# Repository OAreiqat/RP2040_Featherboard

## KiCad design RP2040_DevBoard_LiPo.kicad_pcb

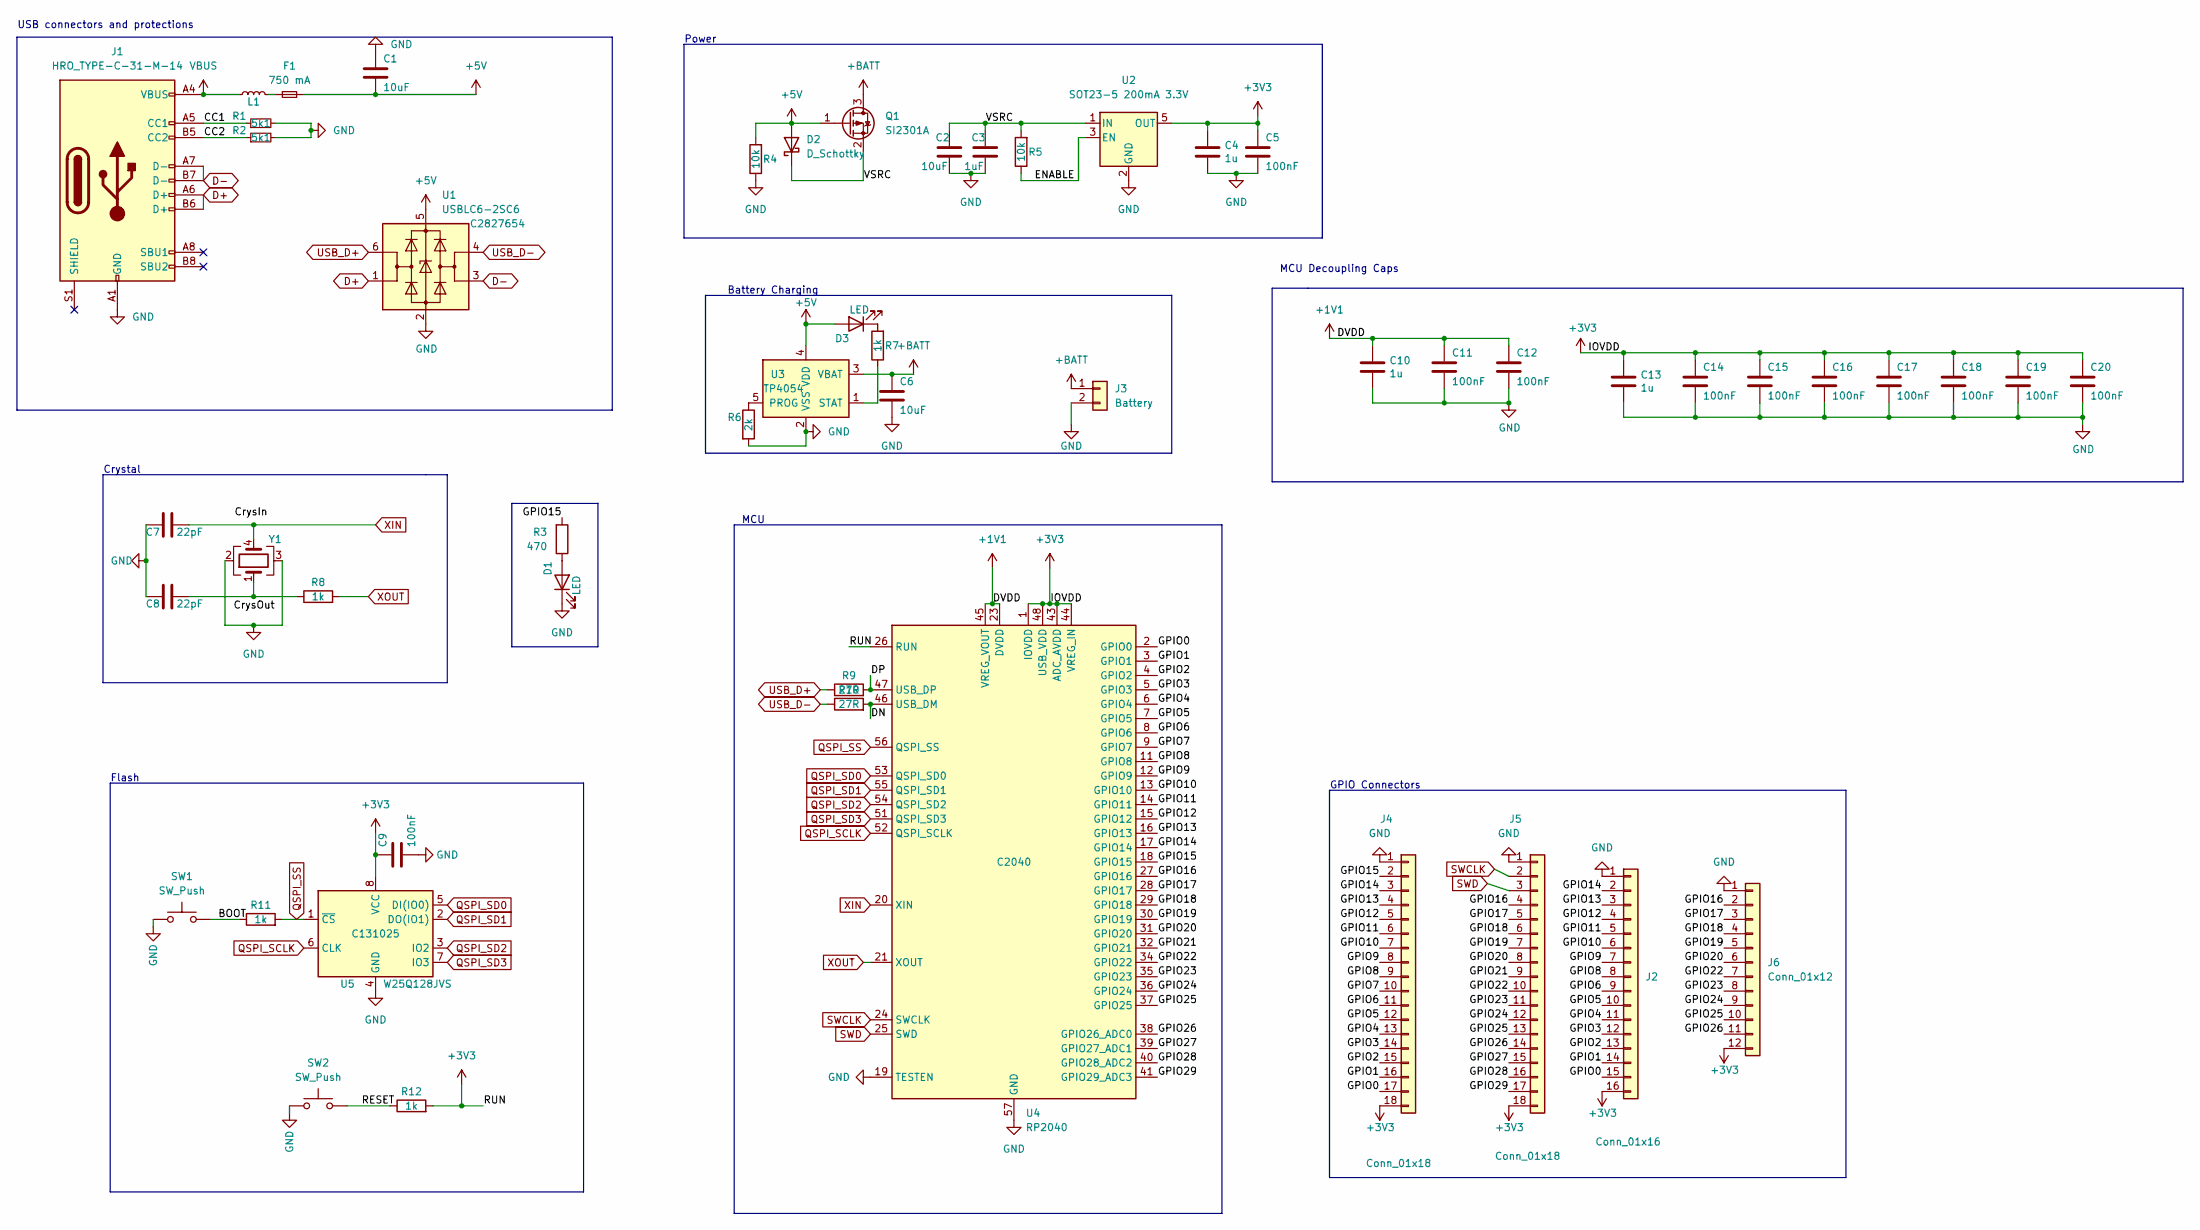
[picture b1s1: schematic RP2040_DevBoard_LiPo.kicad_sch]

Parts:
C1, C2, C6: 10uF; C_0402_1005Metric; LCSC C15525
C3: 1uF; C_0402_1005Metric; LCSC C14445
C4, C10, C13: 1u; C_0402_1005Metric; LCSC C14445
C5, C9, C11, C12, C14, C15, C16, C17, C18, C19, C20: 100nF; C_0402_1005Metric; LCSC C1525
C7, C8: 22pF; C_0402_1005Metric; LCSC C70464
D1, D3: LED; LED_1206_3216Metric; LCSC C434443
D2: D_Schottky; D_SOD-323; LCSC C22624
F1: 750 mA; Fuse_0603_1608Metric; LCSC C182438
J1: HRO_TYPE-C-31-M-14; USB_C_Receptacle_HRO_TYPE-C-31-M-12; LCSC C165948
J2: Conn_01x16; PinSocket_1x16_P2.54mm_Vertical
J3: Battery; JST_EH_S2B-EH_1x02_P2.50mm_Horizontal; LCSC C514173
J4, J5: Conn_01x18; PinSocket_1x18_P2.54mm_Vertical
J6: Conn_01x12; PinSocket_1x12_P2.54mm_Vertical
L1: BLM15PX121SN1D; L_0402_1005Metric; LCSC C88970
Q1: SI2301A; SOT-23; LCSC C347476
R1, R2: 5k1; R_0402_1005Metric; LCSC C25905
R3: 470; R_0402_1005Metric; LCSC C25117
R4, R5: 10k; R_0402_1005Metric; LCSC C60490
R6: 2k; R_0402_1005Metric; LCSC C60488
R7, R8, R11, R12: 1k; R_0402_1005Metric; LCSC C106235
R9, R10: 27R; R_0402_1005Metric; LCSC C3017455
SW1, SW2: SW_Push; SW_Push_SPST_NO_Alps_SKRK; LCSC C720477
U1: USBLC6-2SC6; SOT-23-6; LCSC C2827654
U2: SOT23-5 200mA 3.3V; SOT-23-5; LCSC C11337
U3: TP4054; SOT-23-5; LCSC C668215
U4: RP2040; QFN-56-1EP_7x7mm_P0.4mm_EP3.2x3.2mm; LCSC C2040
U5: W25Q128JVS; SOIC-8_5.23x5.23mm_P1.27mm; LCSC C131025
Y1: Crystal_GND23; Crystal_SMD_3225-4Pin_3.2x2.5mm; LCSC C9002

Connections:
+1V1: C10.1, C11.2, C12.2, U4.23 (DVDD), U4.45 (VREG_VOUT), U4.50 (DVDD)
+3V3: C4.1, C5.2, C9.2, C13.1, C14.2, C15.2, C16.2, C17.2, C18.2, C19.2, C20.2, J2.16, J4.18, J5.18, J6.12, R12.2, U2.5 (OUT), U4.1 (IOVDD), U4.10 (IOVDD), U4.22 (IOVDD), U4.26 (RUN), U4.33 (IOVDD), U4.42 (IOVDD), U4.43 (ADC_AVDD), U4.44 (VREG_IN), U4.48 (USB_VDD), U4.49 (IOVDD), U5.8 (VCC)
+5V: C1.2, D2.2 (A), D3.2 (A), F1.2, Q1.1 (G), R4.2, U1.5 (VBUS), U3.4 (VDD)
+BATT: C6.1, J3.1, Q1.3 (D), U3.3 (VBAT)
/BOOT: R11.1, SW1.2
/CC1: J1.A5 (CC1), R1.1
/CC2: J1.B5 (CC2), R2.1
/DN: R10.2, U4.46 (USB_DM)
/DP: R9.2, U4.47 (USB_DP)
/ENABLE: R5.1, U2.3 (EN)
/GPIO0: J2.15, J4.17, U4.2 (GPIO0)
/GPIO1: J2.14, J4.16, U4.3 (GPIO1)
/GPIO2: J2.13, J4.15, U4.4 (GPIO2)
/GPIO3: J2.12, J4.14, U4.5 (GPIO3)
/GPIO4: J2.11, J4.13, U4.6 (GPIO4)
/GPIO5: J2.10, J4.12, U4.7 (GPIO5)
/GPIO6: J2.9, J4.11, U4.8 (GPIO6)
/GPIO7: J4.10, U4.9 (GPIO7)
/GPIO8: J2.8, J4.9, U4.11 (GPIO8)
/GPIO9: J2.7, J4.8, U4.12 (GPIO9)
/GPIO10: J2.6, J4.7, U4.13 (GPIO10)
/GPIO11: J2.5, J4.6, U4.14 (GPIO11)
/GPIO12: J2.4, J4.5, U4.15 (GPIO12)
/GPIO13: J2.3, J4.4, U4.16 (GPIO13)
/GPIO14: J2.2, J4.3, U4.17 (GPIO14)
/GPIO15: J4.2, R3.2, U4.18 (GPIO15)
/GPIO16: J5.4, J6.2, U4.27 (GPIO16)
/GPIO17: J5.5, J6.3, U4.28 (GPIO17)
/GPIO18: J5.6, J6.4, U4.29 (GPIO18)
/GPIO19: J5.7, J6.5, U4.30 (GPIO19)
/GPIO20: J5.8, J6.6, U4.31 (GPIO20)
/GPIO21: J5.9, U4.32 (GPIO21)
/GPIO22: J5.10, J6.7, U4.34 (GPIO22)
/GPIO23: J5.11, J6.8, U4.35 (GPIO23)
/GPIO24: J5.12, J6.9, U4.36 (GPIO24)
/GPIO25: J5.13, J6.10, U4.37 (GPIO25)
/GPIO26: J5.14, J6.11, U4.38 (GPIO26_ADC0)
/GPIO27: J5.15, U4.39 (GPIO27_ADC1)
/GPIO28: J5.16, U4.40 (GPIO28_ADC2)
/GPIO29: J5.17, U4.41 (GPIO29_ADC3)
/RESET: R12.1, SW2.2
/VSRC: C2.1, C3.1, D2.1 (K), Q1.2 (S), R5.2, U2.1 (IN)
D+: J1.A6 (D+), J1.B6 (D+), U1.1 (I/O1)
D-: J1.A7 (D-), J1.B7 (D-), U1.3 (I/O2)
GND: C1.1, C2.2, C3.2, C4.2, C5.1, C6.2, C7.2, C8.2, C9.1, C10.2, C11.1, C12.1, C13.2, C14.1, C15.1, C16.1, C17.1, C18.1, C19.1, C20.1, D1.1 (K), J1.A1 (GND), J1.A12 (GND), J1.B1 (GND), J1.B12 (GND), J2.1, J3.2, J4.1, J5.1, J6.1, R1.2, R2.2, R4.1, R6.2, SW1.1, SW2.1, U1.2 (GND), U2.2 (GND), U3.2 (VSS), U4.19 (TESTEN), U4.57 (GND), U5.4 (GND), Y1.2, Y1.3
unnamed: C8.1, R8.1, Y1.1
unnamed: D1.2 (A), R3.1
unnamed: D3.1 (K), R7.2
unnamed: F1.1, L1.2
unnamed: R6.1, U3.5 (PROG)
unnamed: R7.1, U3.1 (STAT)
QSPI_SCLK: U4.52 (QSPI_SCLK), U5.6 (CLK)
QSPI_SD0: U4.53 (QSPI_SD0), U5.5 (DI(IO0))
QSPI_SD1: U4.55 (QSPI_SD1), U5.2 (DO(IO1))
QSPI_SD2: U4.54 (QSPI_SD2), U5.3 (IO2)
QSPI_SD3: U4.51 (QSPI_SD3), U5.7 (IO3)
QSPI_SS: R11.2, U4.56 (QSPI_SS), U5.1 (~CS)
SWCLK: J5.2, U4.24 (SWCLK)
SWD: J5.3, U4.25 (SWD)
USB_D+: R9.1, U1.6 (I/O1)
USB_D-: R10.1, U1.4 (I/O2)
VBUS: J1.A4 (VBUS), J1.A9 (VBUS), J1.B4 (VBUS), J1.B9 (VBUS), L1.1
XIN: C7.1, U4.20 (XIN), Y1.4
XOUT: R8.2, U4.21 (XOUT)

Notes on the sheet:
USB connectors and protections
Battery Charging
Crystal
MCU
MCU Decoupling Caps
Flash
Power
GPIO Connectors

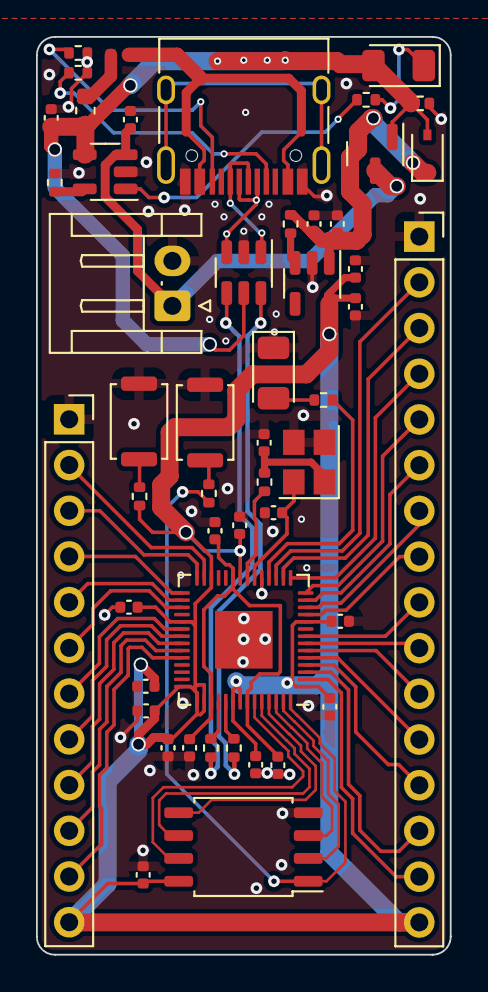
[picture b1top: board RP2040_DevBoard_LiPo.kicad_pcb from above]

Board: 2 copper layers, 23.0 x 51.0 mm, 50 parts (0 on the bottom side), 57 nets.

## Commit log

2023-01-03 added missing 3v3 arrow, changed some footprints
2023-01-04 Updated Schematic. Added LCSC part for most parts
2023-01-04 started routing
2023-01-04 Finished routing Featherboard
2023-01-06 added adjustments to vias around the board
